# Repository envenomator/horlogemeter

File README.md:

# Horlogemeter

Ontwerp en code voor een meetinstrument die de tijdsafwijking aangeeft van een analoog uurwerk, gebaseerd op een Atmega328p

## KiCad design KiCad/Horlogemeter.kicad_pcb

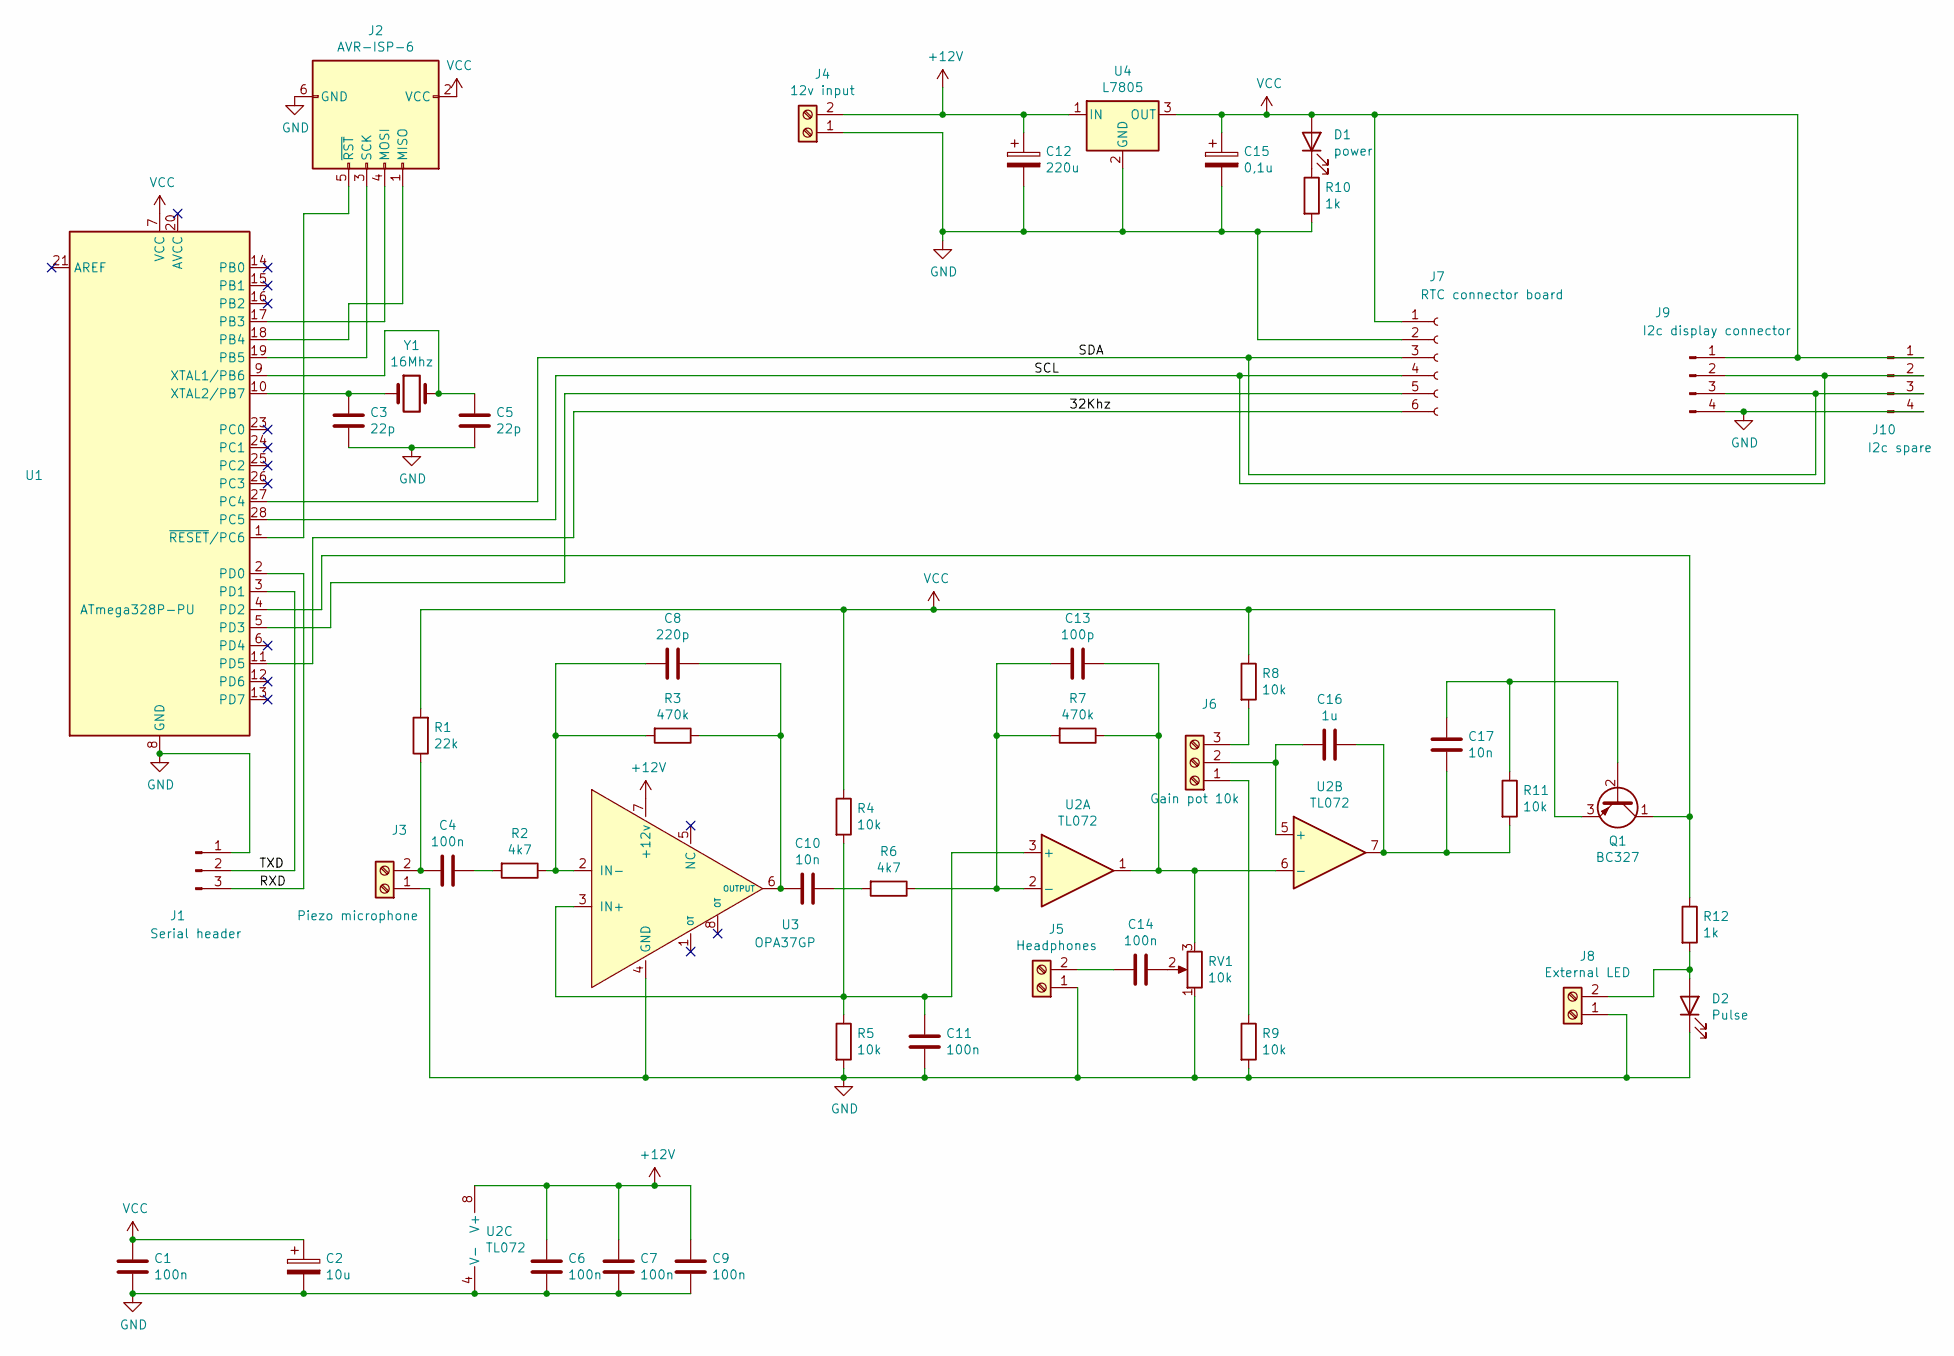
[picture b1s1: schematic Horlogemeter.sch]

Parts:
C1, C4, C6, C7, C9, C11, C14: 100n; C_Disc_D3.4mm_W2.1mm_P2.50mm
C2: 10u; CP_Radial_D5.0mm_P2.50mm
C3, C5: 22p; C_Disc_D3.4mm_W2.1mm_P2.50mm
C8: 220p; C_Disc_D3.4mm_W2.1mm_P2.50mm
C10, C17: 10n; C_Disc_D3.4mm_W2.1mm_P2.50mm
C12: 220u; CP_Radial_D5.0mm_P2.50mm
C13: 100p; C_Disc_D3.4mm_W2.1mm_P2.50mm
C15: 0,1u; CP_Radial_D5.0mm_P2.50mm
C16: 1u; C_Disc_D3.4mm_W2.1mm_P2.50mm
D1: power; LED_D3.0mm
D2: Pulse; LED_D3.0mm
J1: Serial header; PinHeader_1x03_P2.54mm_Vertical
J2: AVR-ISP-6; PinHeader_2x03_P2.54mm_Vertical
J3: Piezo microphone; TerminalBlock_bornier-2_P5.08mm
J4: 12v input; TerminalBlock_bornier-2_P5.08mm
J5: Headphones; TerminalBlock_bornier-2_P5.08mm
J6: Gain pot 10k; TerminalBlock_bornier-3_P5.08mm
J7: RTC connector board; PinSocket_1x06_P2.54mm_Horizontal
J8: External LED; TerminalBlock_bornier-2_P5.08mm
J9: I2c display connector; PinHeader_1x04_P2.54mm_Vertical
J10: I2c spare; PinHeader_1x04_P2.54mm_Vertical
Q1: BC327; TO-92_Inline_Wide
R1: 22k; R_Axial_DIN0207_L6.3mm_D2.5mm_P7.62mm_Horizontal
R2, R6: 4k7; R_Axial_DIN0207_L6.3mm_D2.5mm_P7.62mm_Horizontal
R3, R7: 470k; R_Axial_DIN0207_L6.3mm_D2.5mm_P7.62mm_Horizontal
R4, R5, R8, R9, R11: 10k; R_Axial_DIN0207_L6.3mm_D2.5mm_P7.62mm_Horizontal
R10, R12: 1k; R_Axial_DIN0207_L6.3mm_D2.5mm_P7.62mm_Horizontal
RV1: 10k; Potentiometer_Piher_PT-10-V05_Vertical
U1: ATmega328P-PU; DIP-28_W7.62mm
U2: TL072; DIP-8_W7.62mm
U3: OPA37GP; DIP-8_W7.62mm
U4: L7805; TO-220-3_Horizontal_TabDown
Y1: 16Mhz; Crystal_HC18-U_Vertical

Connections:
+12V: C6.1, C7.1, C9.1, C12.1, J4.2, U2.8 (V+), U3.7 (+12v), U4.1 (IN)
/32Khz: J7.6, U1.11 (PD5)
/RXD: J1.3, U1.2 (PD0)
/SCL: J7.4, J9.2, J10.2, U1.28 (PC5)
/SDA: J7.3, J9.3, J10.3, U1.27 (PC4)
/TXD: J1.2, U1.3 (PD1)
GND: C1.2, C2.2, C3.2, C5.2, C6.2, C7.2, C9.2, C11.2, C12.2, C15.2, D2.1 (K), J1.1, J2.6 (GND), J3.1, J4.1, J5.1, J7.2, J8.1, J9.4, J10.4, R5.2, R9.2, R10.2, RV1.1, U1.8 (GND), U1.22 (GND), U2.4 (V-), U3.4 (GND), U4.2 (GND)
unnamed: C3.1, U1.10 (XTAL2/PB7), Y1.1
unnamed: C4.1, J3.2, R1.1
unnamed: C4.2, R2.2
unnamed: C5.1, U1.9 (XTAL1/PB6), Y1.2
unnamed: C8.2, R2.1, R3.2, U3.2 (IN-)
unnamed: C10.1, R6.2
unnamed: C8.1, C10.2, R3.1, U3.6 (OUTPUT)
unnamed: C11.1, R4.2, R5.1, U2.3 (+), U3.3 (IN+)
unnamed: C13.1, R7.1, RV1.3, U2.1, U2.6 (-)
unnamed: C13.2, R6.1, R7.2, U2.2 (-)
unnamed: C14.1, RV1.2
unnamed: C14.2, J5.2
unnamed: C16.1, C17.1, R11.2, U2.7
unnamed: C16.2, J6.2, U2.5 (+)
unnamed: C17.2, Q1.2 (B), R11.1
unnamed: D1.1 (K), R10.1
unnamed: D2.2 (A), J8.2, R12.2
unnamed: J2.1 (MISO), U1.18 (PB4)
unnamed: J2.3 (SCK), U1.19 (PB5)
unnamed: J2.4 (MOSI), U1.17 (PB3)
unnamed: J2.5 (~RST), U1.1 (~RESET~/PC6)
unnamed: J6.1, R9.1
unnamed: J6.3, R8.2
unnamed: J7.5, U1.5 (PD3)
unnamed: Q1.1 (C), R12.1, U1.4 (PD2)
VCC: C1.1, C2.1, C15.1, D1.2 (A), J2.2 (VCC), J7.1, J9.1, J10.1, Q1.3 (E), R1.2, R4.1, R8.1, U1.7 (VCC), U4.3 (OUT)

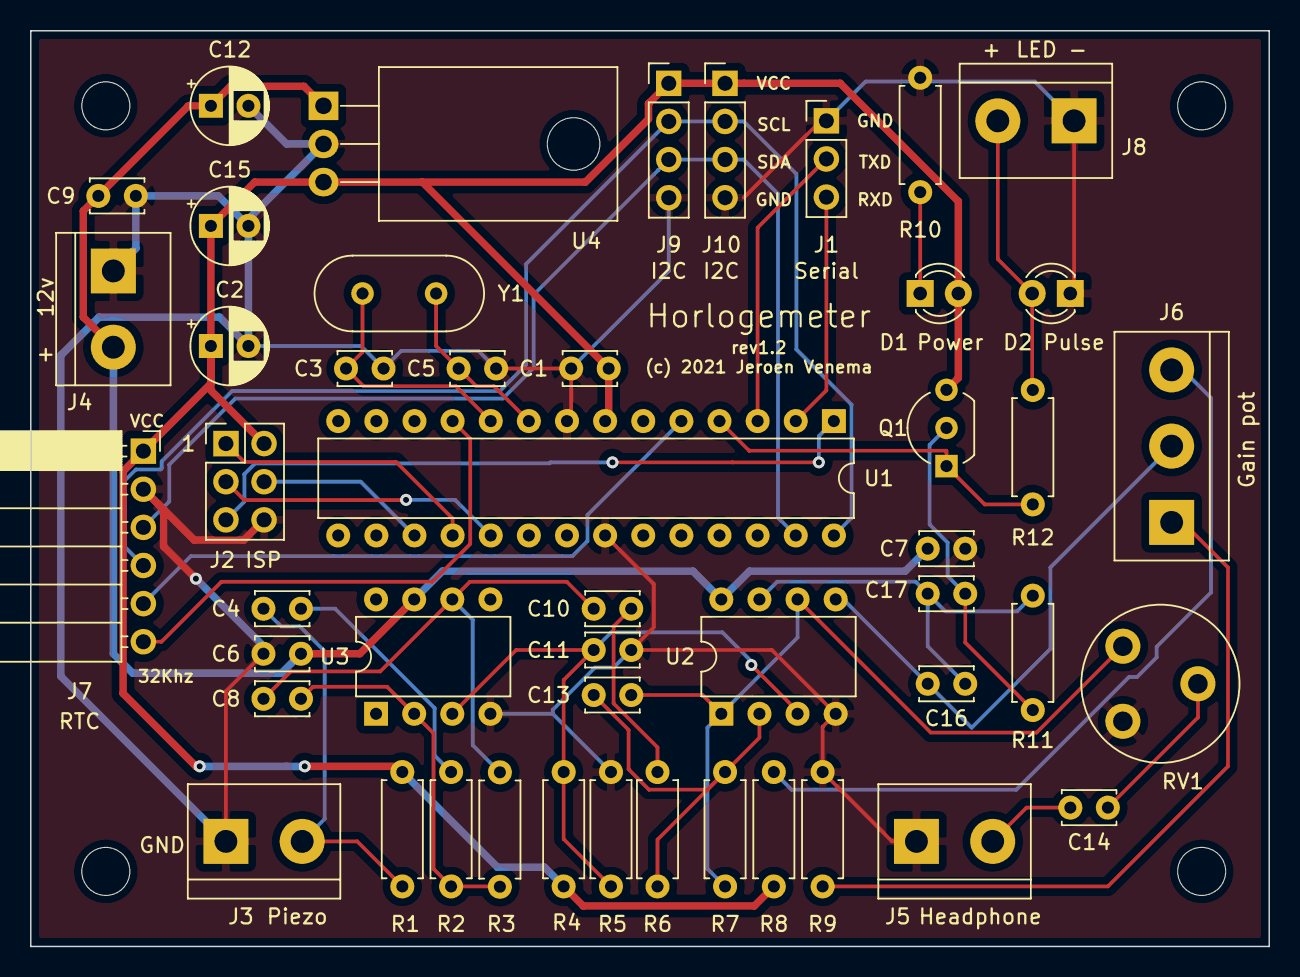
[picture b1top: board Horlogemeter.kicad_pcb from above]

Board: 2 copper layers, 82.5 x 61.0 mm, 48 parts (0 on the bottom side), 33 nets.

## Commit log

2021-01-03 Added .gitignore
2021-01-03 Removed ignored files
2021-01-03 Removed hex files
2021-01-10 usable base, display of deviation in secs/day, unsigned
2021-01-13 Working base - changed to PlatformIO
2021-01-14 Added 20x4 LCD display
2021-01-14 Schema aangepast
2021-01-15 Schema checked, netlist created
2021-01-15 PCB v1.1 created
2021-01-16 Created new PCB with Gerbers
2021-01-25 R12 to 1K / C16 to ceramic
2021-01-25 Revision to 1.2
2021-05-24 Different average method complete
2021-05-24 Changed highest tickvalue competition
2021-05-24 defines optimization
2021-05-24 code cleanup
2021-08-23 Redesign complete
2021-08-24 Averaging functional improved

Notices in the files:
KiCad/Horlogemeter.kicad_pcb:
(c) 2021 Jeroen Venema
